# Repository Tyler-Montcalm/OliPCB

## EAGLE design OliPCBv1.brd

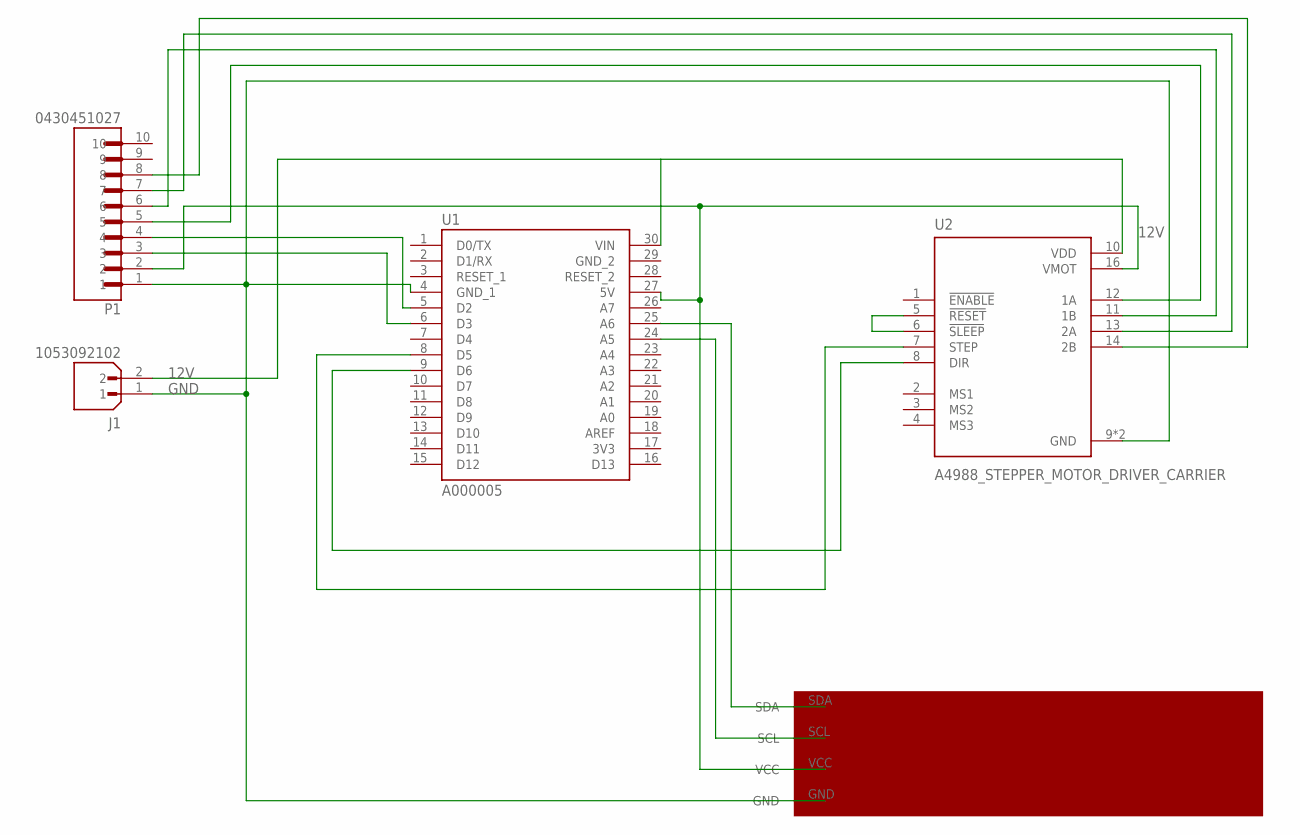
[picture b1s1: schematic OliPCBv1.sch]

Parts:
J1: 1053092102; MOLEX_1053092102
P1: 0430451027; MOLEX_0430451027
U1: A000005; MODULE_A000005
U2: A4988_STEPPER_MOTOR_DRIVER_CARRIER; MODULE_A4988_STEPPER_MOTOR_DRIVER_CARRIER
U$1: WYTP61_DEVICE; WTYP61

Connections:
3V3: U1.17 (3V3)
12V: J1.2, U1.30 (VIN), U2.10 (VDD)
GND: J1.1, P1.1, U1.4 (GND_1), U2.9 (GND), U2.15 (GND), U$1.GND
GND_2: U1.29 (GND_2)
unnamed: U1.9 (D6), U2.8 (DIR)
unnamed: U1.8 (D5), U2.7 (STEP)
unnamed: U1.24 (A5), U$1.SCL
unnamed: U1.25 (A6), U$1.SDA
unnamed: P1.2, U1.27 (5V), U2.16 (VMOT), U$1.VCC
unnamed: P1.3, U1.6 (D3)
unnamed: P1.4, U1.5 (D2)
unnamed: P1.5, U2.12 (1A)
unnamed: P1.6, U2.11 (1B)
unnamed: P1.7, U2.13 (2A)
unnamed: P1.8, U2.14 (2B)
unnamed: U2.5 (!RESET), U2.6 (!SLEEP)

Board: 2 copper layers, 5 parts (0 on the bottom side), 14 nets, no tracks yet.

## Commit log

2022-03-23 YE
    s
